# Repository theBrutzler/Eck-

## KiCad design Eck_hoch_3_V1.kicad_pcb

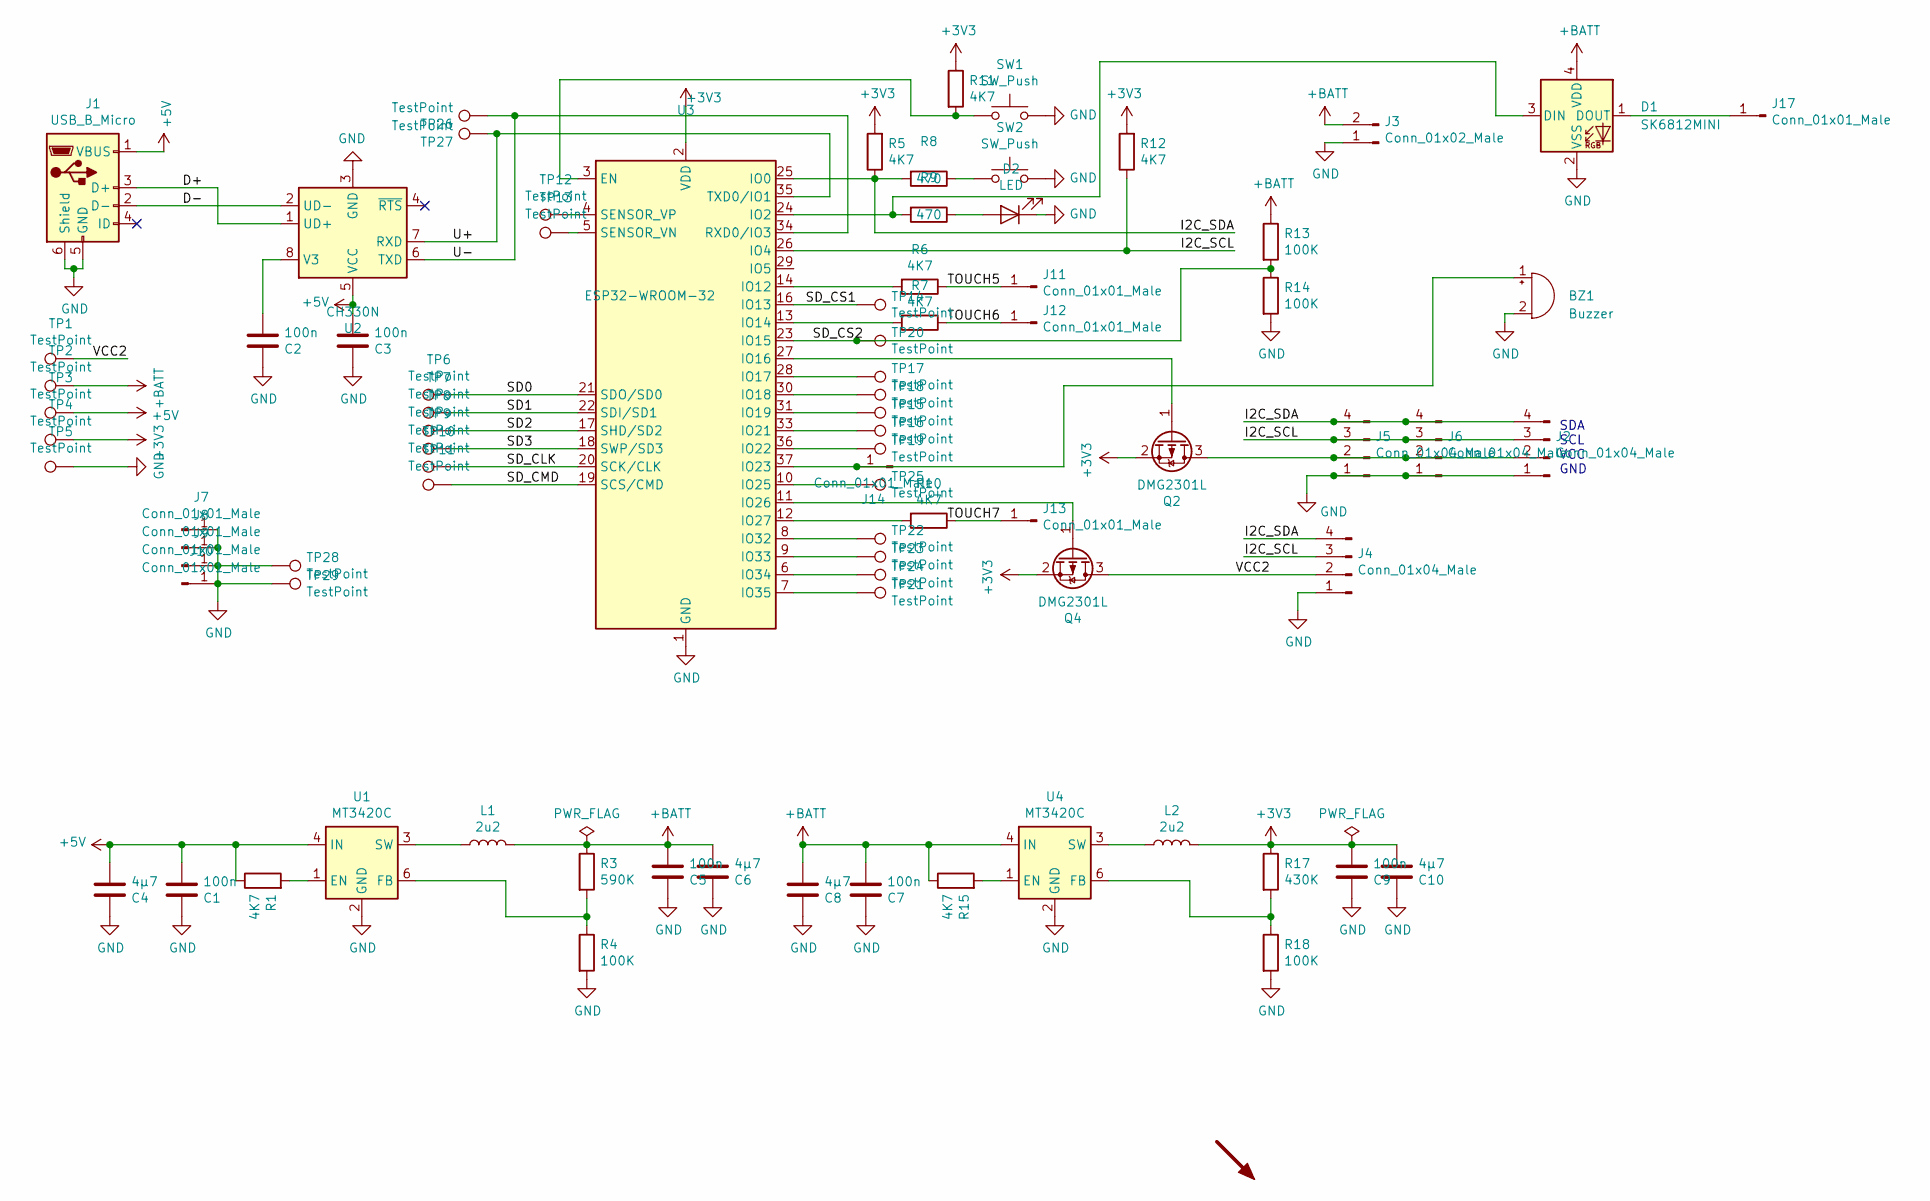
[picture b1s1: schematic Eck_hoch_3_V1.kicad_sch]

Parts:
BZ1: Buzzer; MagneticBuzzer_MLT-5030
C1, C2, C3, C5, C7, C9: 100n; C_0603_1608Metric
C4, C6, C8, C10: 4µ7; C_0603_1608Metric
D1: SK6812MINI; LED_SK6812MINI_PLCC4_3.5x3.5mm_P1.75mm
D2: LED; LED_1206_3216Metric
J1: USB_B_Micro; USB_Micro-B_Amphenol_10118194_Horizontal
J2: Conn_01x04_Male; SSD1306_0.96_I2C
J3: Conn_01x02_Male; PinHeader_1x02_P2.54mm_Vertical
J4, J5, J6: Conn_01x04_Male; PinHeader_1x04_P2.54mm_Vertical
J7, J8, J9, J10, J11, J12, J13, J14, J17: Conn_01x01_Male; PinHeader_1x01_P2.54mm_Vertical
L1, L2: 2u2; L_1210_3225Metric
Q2, Q4: DMG2301L; SOT-23
R1, R5, R6, R7, R10, R11, R12, R15: 4K7; R_0603_1608Metric
R3: 590K; R_0603_1608Metric
R4, R13, R14, R18: 100K; R_0603_1608Metric
R8, R9: 470; R_0603_1608Metric
R17: 430K; R_0603_1608Metric
SW1, SW2: SW_Push; Panasonic_EVQPUL_EVQPUC
TP1, TP2, TP3, TP4, TP6, TP7, TP8, TP9, TP10, TP11, TP12, TP13, TP14, TP15, TP16, TP17, TP18, TP19, TP20, TP21, TP22, TP23, TP24, TP25, TP26, TP27, TP28, TP29: TestPoint; TestPoint_Pad_D1.5mm
TP5: TestPoint; TestPoint_Pad_1.5x1.5mm
U1, U4: MT3420C; SOT-23-6
U2: CH330N; SOIC-8_3.9x4.9mm_P1.27mm
U3: ESP32-WROOM-32

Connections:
+3V3: C9.2, C10.2, L2.2, Q2.2 (S), Q4.2 (S), R5.2, R11.1, R12.2, R17.1, TP4.1, U3.2 (VDD)
+5V: C1.2, C3.2, C4.2, J1.1 (VBUS), R1.1, TP3.1, U1.4 (IN), U2.5 (VCC)
+BATT: C5.2, C6.2, C7.2, C8.2, D1.4 (VDD), J3.2, L1.2, R3.1, R13.1, R15.1, TP2.1, U4.4 (IN)
/D+: J1.3 (D+), U2.1 (UD+)
/D-: J1.2 (D-), U2.2 (UD-)
/I2C_SCL: J2.3, J4.3, J5.3, J6.3, R12.1, U3.26 (IO4)
/I2C_SDA: J2.4, J4.4, J5.4, J6.4, R5.1, R8.2, U3.25 (IO0)
/SD0: TP6.1, U3.21 (SDO/SD0)
/SD1: TP7.1, U3.22 (SDI/SD1)
/SD2: TP8.1, U3.17 (SHD/SD2)
/SD3: TP9.1, U3.18 (SWP/SD3)
/SD_CLK: TP10.1, U3.20 (SCK/CLK)
/SD_CMD: TP11.1, U3.19 (SCS/CMD)
/SD_CS1: TP14.1, U3.16 (IO13)
/SD_CS2: R13.2, R14.1, TP20.1, U3.23 (IO15)
/TOUCH5: J11.1, R6.1
/TOUCH6: J12.1, R7.1
/TOUCH7: J13.1, R10.1
/U+: TP27.1, U2.7 (RXD), U3.35 (TXD0/IO1)
/U-: TP26.1, U2.6 (TXD), U3.34 (RXD0/IO3)
/VCC2: J4.2, Q4.3 (D), TP1.1
GND: BZ1.2 (+), C1.1, C2.2, C3.1, C4.1, C5.1, C6.1, C7.1, C8.1, C9.1, C10.1, D1.2 (VSS), D2.1 (K), J1.5 (GND), J1.6 (Shield), J2.1, J3.1, J4.1, J5.1, J6.1, J7.1, J8.1, J9.1, J10.1, R4.2, R14.2, R18.2, SW1.2, SW2.2, TP5.1, TP28.1, TP29.1, U1.2 (GND), U2.3 (GND), U3.1 (GND), U3.15 (GND), U3.38 (GND), U3.39 (GND), U4.2 (GND)
unnamed: BZ1.1 (-), J14.1, U3.37 (IO23)
unnamed: C2.1, U2.8 (V3)
unnamed: D1.1 (DOUT), J17.1
unnamed: D1.3 (DIN), R9.2, U3.24 (IO2)
unnamed: D2.2 (A), R9.1
unnamed: J2.2, J5.2, J6.2, Q2.3 (D)
unnamed: L1.1, U1.3 (SW)
unnamed: L2.1, U4.3 (SW)
unnamed: Q2.1 (G), U3.27 (IO16)
unnamed: Q4.1 (G), U3.11 (IO26)
unnamed: R1.2, U1.1 (EN)
unnamed: R3.2, R4.1, U1.6 (FB)
unnamed: R6.2, U3.14 (IO12)
unnamed: R7.2, U3.13 (IO14)
unnamed: R8.1, SW2.1
unnamed: R10.2, U3.12 (IO27)
unnamed: R11.2, SW1.1, U3.3 (EN)
unnamed: R15.2, U4.1 (EN)
unnamed: R17.2, R18.1, U4.6 (FB)
unnamed: TP12.1, U3.4 (SENSOR_VP)
unnamed: TP13.1, U3.5 (SENSOR_VN)
unnamed: TP15.1, U3.31 (IO19)
unnamed: TP16.1, U3.33 (IO21)
unnamed: TP17.1, U3.28 (IO17)
unnamed: TP18.1, U3.30 (IO18)
unnamed: TP19.1, U3.36 (IO22)
unnamed: TP21.1, U3.7 (IO35)
unnamed: TP22.1, U3.8 (IO32)
unnamed: TP23.1, U3.9 (IO33)
unnamed: TP24.1, U3.6 (IO34)
unnamed: TP25.1, U3.10 (IO25)
no_connect_(J1-Pad4): J1.4 (ID)
no_connect_(U1-Pad5): U1.5 (NC)
no_connect_(U2-Pad4): U2.4 (~RTS)
no_connect_(U3-Pad29): U3.29 (IO5)
no_connect_(U3-Pad32): U3.32 (NC)
no_connect_(U4-Pad5): U4.5 (NC)

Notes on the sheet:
SDA SCL VCC GND

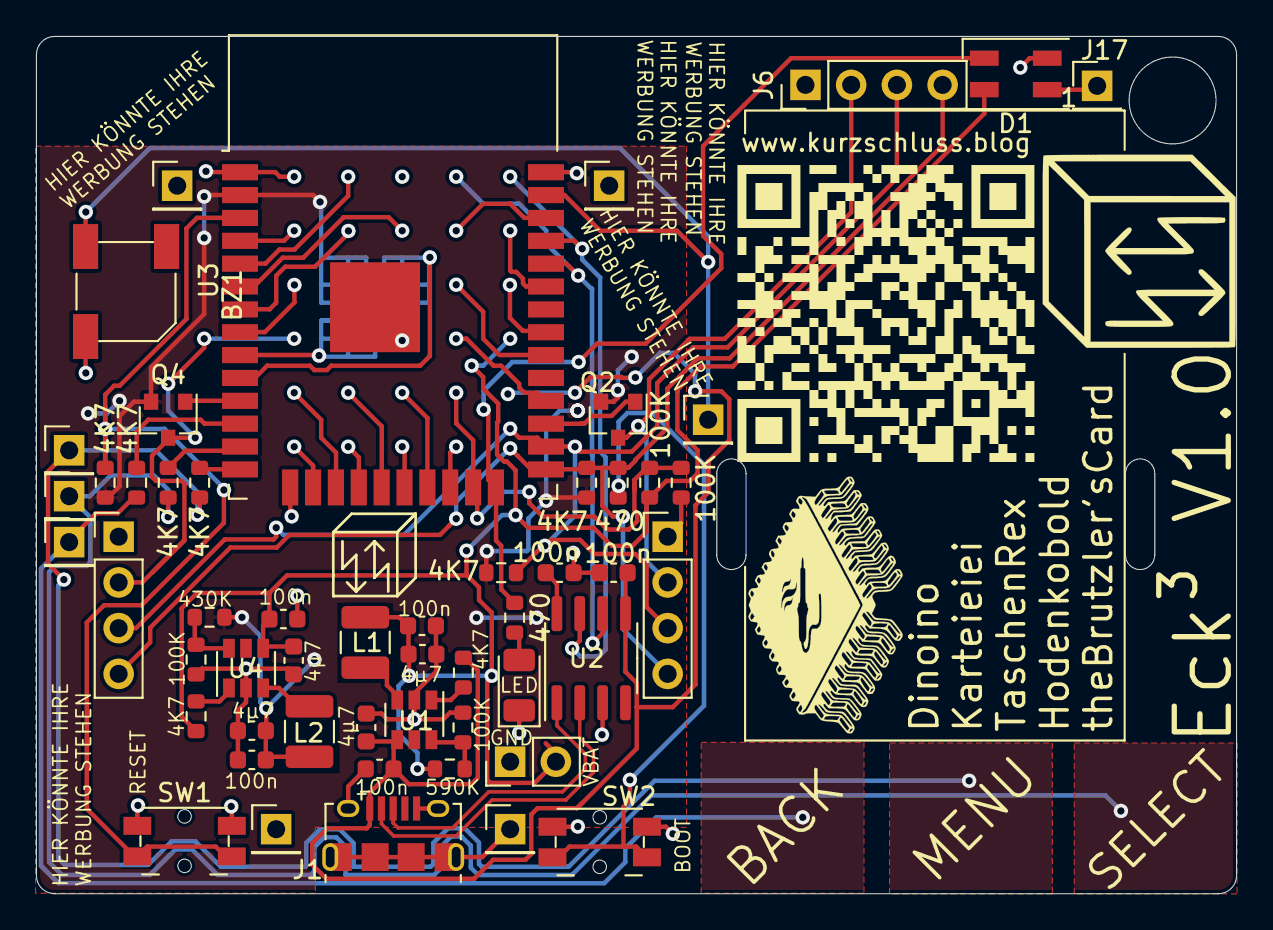
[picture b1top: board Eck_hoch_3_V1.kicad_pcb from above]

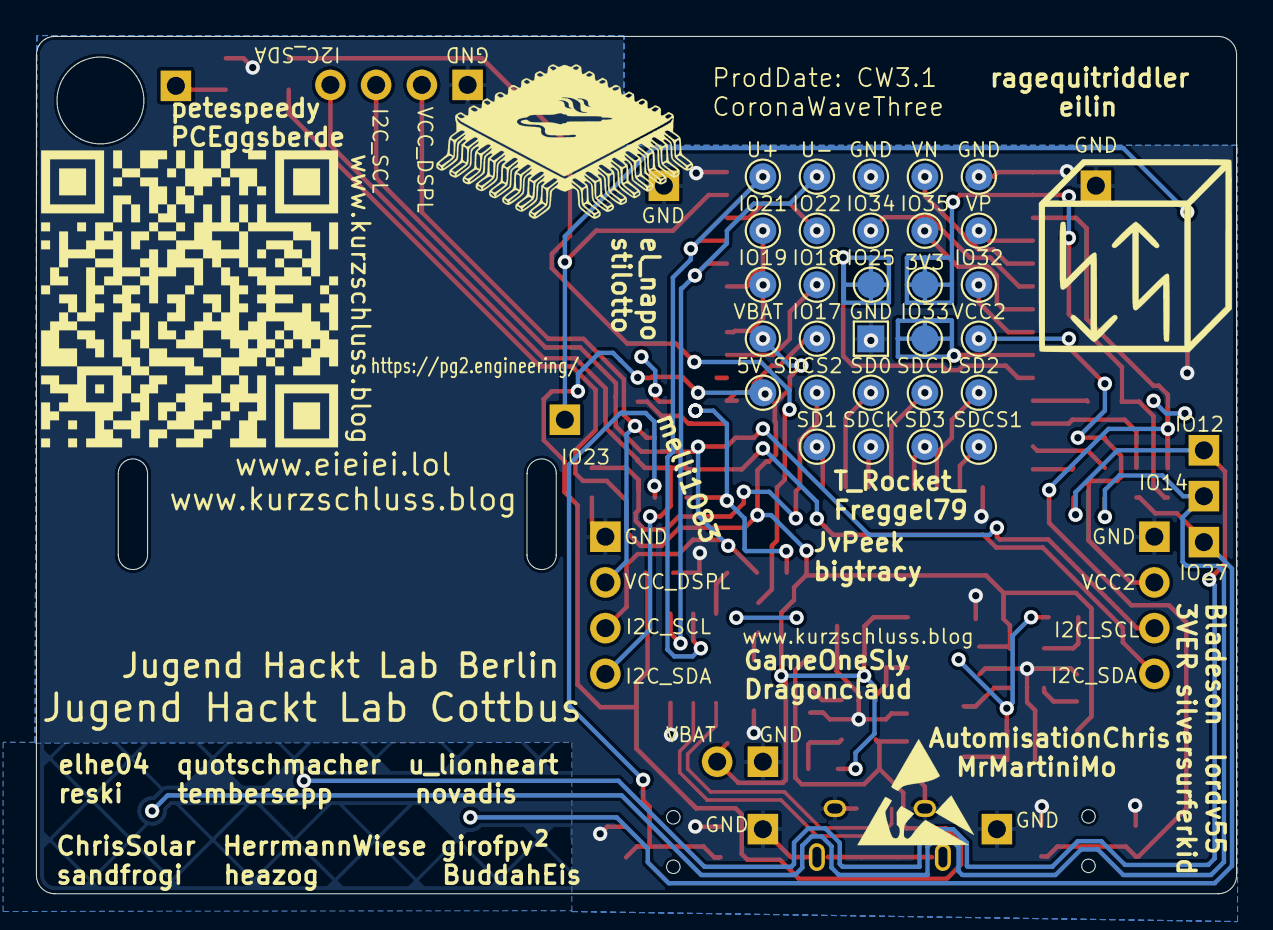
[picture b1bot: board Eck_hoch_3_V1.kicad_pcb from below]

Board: 2 copper layers, 66.7 x 47.6 mm, 85 parts (30 on the bottom side), 53 nets.

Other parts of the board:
QR*****: www.kurzschluss.blog
QR*****#2: www.kurzschluss.blog
SM3: SYM_Arrow45_Tiny; Symbol_kurzschlussblog

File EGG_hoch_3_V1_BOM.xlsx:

Comment | Designator | Footprint | LCSC-Part# | Qty
100n | C1, C2, C3, C5, C7, C9 | 0603_C | C14663 | 6
4µ7 | C4, C6, C8, C10 | 0603_C | C1705 | 4
LED | D2 | 1206_LED | C375461 | 1
USB_B_Micro | J1 | USB_Micro-B | C404969 | 1
2u2 | L1, L2 | 1210_L | C86074 | 2
DMG2301L | Q2, Q4 | SOT-23 | C508195 | 2
590K | R3 | 0603_R | C23208 | 1
100K | R4, R13, R14, R18 | 0603_R | C25803 | 4
470 | R8, R9 | 0603_R | C23179 | 2
4K7 | R1, R5, R6, R7, R10, R11, R12, R15 | 0603_R | C23162 | 8
430K | R17 | 0603_R | C25969 | 1
SW_Push | SW1, SW2 | Switch_SMD | C221907 | 2
MT3420C | U1, U4 | SOT-23-6 | C181741 | 2
CH330N | U2 | SOIC-8 | C108996 | 1
ESP32-WROOM-32 | U3 | ESP32-WROOM-32 | C82899 | 1
Buzzer | BZ1 | 5030 | C94598 | 1

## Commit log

2021-06-09 Initial Upload
